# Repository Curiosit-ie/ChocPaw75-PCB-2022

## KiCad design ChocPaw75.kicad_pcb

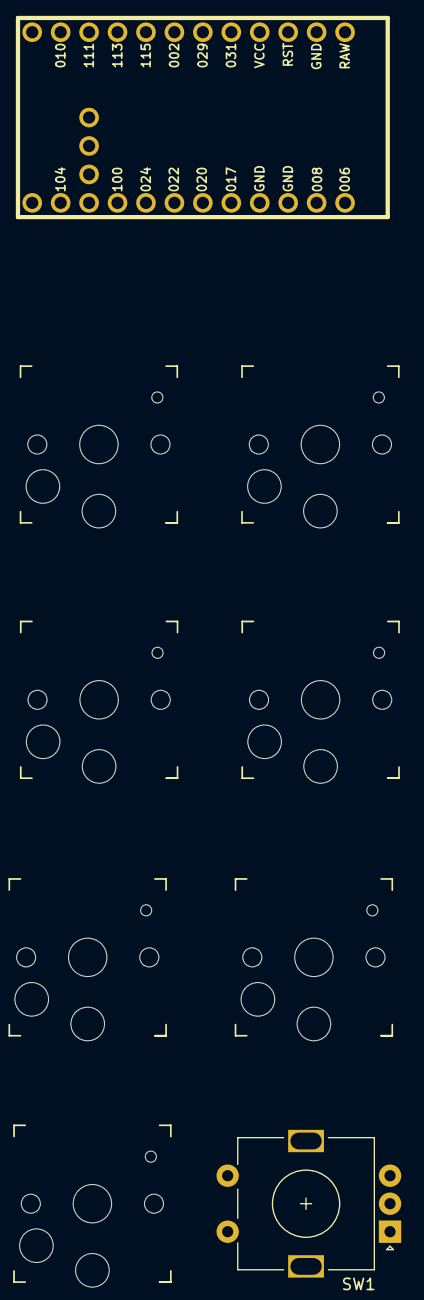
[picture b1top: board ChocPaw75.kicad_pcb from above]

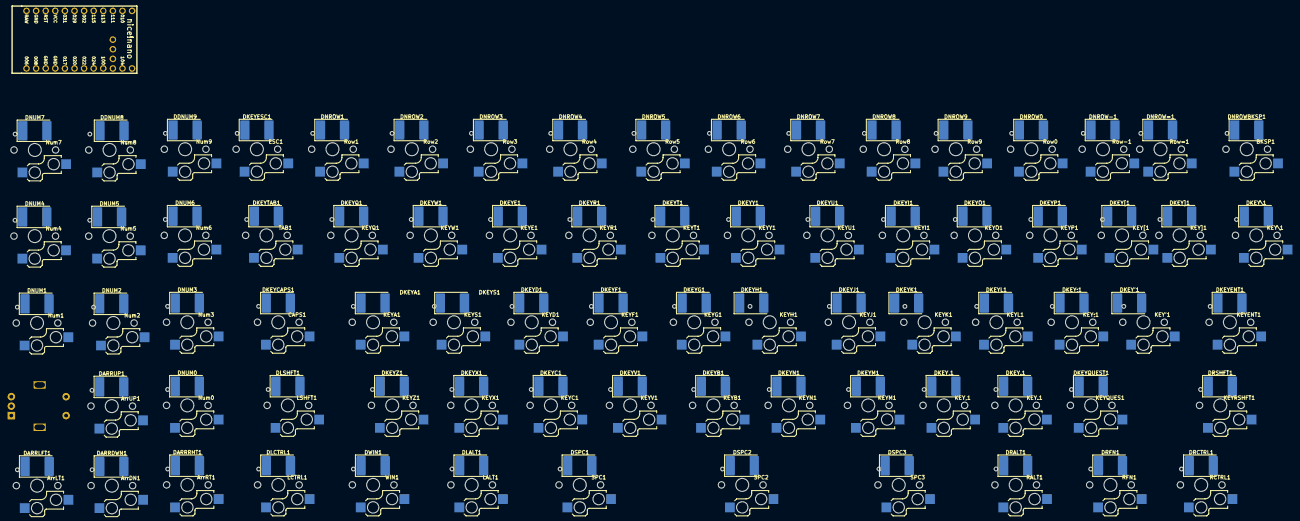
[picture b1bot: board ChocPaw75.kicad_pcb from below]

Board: 2 copper layers, 154 parts (77 on the bottom side), 98 nets, no tracks yet.

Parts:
ArrDN1: Arrow DOWN; Kailh_socket_PG1350
ArrLT1: Arrow LEFT; Kailh_socket_PG1350
ArrRT1: Arrow RIGHT; Kailh_socket_PG1350
ArrUP1: Arrow UP; Kailh_socket_PG1350
BKSP1: MX-LED; Kailh_socket_PG1350
CAPS1: MX-LED; Kailh_socket_PG1350
DARRDWN1: D_Small; D_3220_8050Metric
DARRLFT1: D_Small; D_3220_8050Metric
DARRRHT1: D_Small; D_3220_8050Metric
DARRUP1: D_Small; D_3220_8050Metric
DDNUM8, DDNUM9: D_Small; D_3220_8050Metric
DKEY'1: D_Small; D_3220_8050Metric
DKEY,1: D_Small; D_3220_8050Metric
DKEY.1: D_Small; D_3220_8050Metric
DKEY;1: D_Small; D_3220_8050Metric
DKEYA1: D_Small; D_3220_8050Metric
DKEYB1: D_Small; D_3220_8050Metric
DKEYC1: D_Small; D_3220_8050Metric
DKEYCAPS1: D_Small; D_3220_8050Metric
DKEYD1: D_Small; D_3220_8050Metric
DKEYE1: D_Small; D_3220_8050Metric
DKEYENT1: D_Small; D_3220_8050Metric
DKEYESC1: D_Small; D_3220_8050Metric
DKEYF1: D_Small; D_3220_8050Metric
DKEYG1: D_Small; D_3220_8050Metric
DKEYH1: D_Small; D_3220_8050Metric
DKEYI1: D_Small; D_3220_8050Metric
DKEYJ1: D_Small; D_3220_8050Metric
DKEYK1: D_Small; D_3220_8050Metric
DKEYL1: D_Small; D_3220_8050Metric
DKEYM1: D_Small; D_3220_8050Metric
DKEYN1: D_Small; D_3220_8050Metric
DKEYO1: D_Small; D_3220_8050Metric
DKEYP1: D_Small; D_3220_8050Metric
DKEYQ1: D_Small; D_3220_8050Metric
DKEYQUEST1: D_Small; D_3220_8050Metric
DKEYR1: D_Small; D_3220_8050Metric
DKEYS1: D_Small; D_3220_8050Metric
DKEYT1: D_Small; D_3220_8050Metric
DKEYTAB1: D_Small; D_3220_8050Metric
DKEYU1: D_Small; D_3220_8050Metric
DKEYV1: D_Small; D_3220_8050Metric
DKEYW1: D_Small; D_3220_8050Metric
DKEYX1: D_Small; D_3220_8050Metric
DKEYY1: D_Small; D_3220_8050Metric
DKEYZ1: D_Small; D_3220_8050Metric
DKEY[1: D_Small; D_3220_8050Metric
DKEY\1: D_Small; D_3220_8050Metric
DKEY]1: D_Small; D_3220_8050Metric
DLALT1: D_Small; D_3220_8050Metric
DLCTRL1: D_Small; D_3220_8050Metric
DLSHFT1: D_Small; D_3220_8050Metric
DNROW0, DNROW1, DNROW2, DNROW3, DNROW4, DNROW5, DNROW6, DNROW7, DNROW8, DNROW9: D_Small; D_3220_8050Metric
DNROW-1: D_Small; D_3220_8050Metric
DNROW=1: D_Small; D_3220_8050Metric
DNROWBKSP1: D_Small; D_3220_8050Metric
DNUM0, DNUM1, DNUM2, DNUM3, DNUM4, DNUM5, DNUM6, DNUM7: D_Small; D_3220_8050Metric
DRALT1: D_Small; D_3220_8050Metric
DRCTRL1: D_Small; D_3220_8050Metric
DRFN1: D_Small; D_3220_8050Metric
DRSHFT1: D_Small; D_3220_8050Metric
DSPC1, DSPC2, DSPC3: D_Small; D_3220_8050Metric
DWIN1: D_Small; D_3220_8050Metric
ESC1: MX-LED; Kailh_socket_PG1350
KEY'1: MX-LED; Kailh_socket_PG1350
KEY,1: MX-LED; Kailh_socket_PG1350
KEY.1: MX-LED; Kailh_socket_PG1350
KEY;1: MX-LED; Kailh_socket_PG1350
KEYA1: MX-LED; Kailh_socket_PG1350
KEYB1: MX-LED; Kailh_socket_PG1350
KEYC1: MX-LED; Kailh_socket_PG1350
KEYD1: MX-LED; Kailh_socket_PG1350
KEYE1: MX-LED; Kailh_socket_PG1350
KEYENT1: MX-LED; Kailh_socket_PG1350
KEYF1: MX-LED; Kailh_socket_PG1350
KEYG1: MX-LED; Kailh_socket_PG1350
KEYH1: MX-LED; Kailh_socket_PG1350
KEYI1: MX-LED; Kailh_socket_PG1350
KEYJ1: MX-LED; Kailh_socket_PG1350
KEYK1: MX-LED; Kailh_socket_PG1350
KEYL1: MX-LED; Kailh_socket_PG1350
KEYM1: MX-LED; Kailh_socket_PG1350
KEYN1: MX-LED; Kailh_socket_PG1350
KEYO1: MX-LED; Kailh_socket_PG1350
KEYP1: MX-LED; Kailh_socket_PG1350
KEYQ1: MX-LED; Kailh_socket_PG1350
KEYQUES1: MX-LED; Kailh_socket_PG1350
KEYR1: MX-LED; Kailh_socket_PG1350
KEYRSHFT1: MX-LED; Kailh_socket_PG1350
KEYS1: MX-LED; Kailh_socket_PG1350
KEYT1: MX-LED; Kailh_socket_PG1350
KEYU1: MX-LED; Kailh_socket_PG1350
KEYV1: MX-LED; Kailh_socket_PG1350
KEYW1: MX-LED; Kailh_socket_PG1350
KEYX1: MX-LED; Kailh_socket_PG1350
KEYY1: MX-LED; Kailh_socket_PG1350
KEYZ1: MX-LED; Kailh_socket_PG1350
KEY[1: MX-LED; Kailh_socket_PG1350
KEY\1: MX-LED; Kailh_socket_PG1350
KEY]1: MX-LED; Kailh_socket_PG1350
LALT1: MX-LED; Kailh_socket_PG1350
LCTRL1: MX-LED; Kailh_socket_PG1350
LSHFT1: MX-LED; Kailh_socket_PG1350
Num0: Num 0; Kailh_socket_PG1350
Num1: Num 1; Kailh_socket_PG1350
Num2: Num 2; Kailh_socket_PG1350
Num3: Num 3; Kailh_socket_PG1350
Num4: Num 4; Kailh_socket_PG1350
Num5: Num 5; Kailh_socket_PG1350
Num6: Num 6; Kailh_socket_PG1350
Num7: Num 7; Kailh_socket_PG1350
Num8: Num 8; Kailh_socket_PG1350
Num9: Num 9; Kailh_socket_PG1350
RALT1: MX-LED; Kailh_socket_PG1350
RCTRL1: MX-LED; Kailh_socket_PG1350
RFN1: MX-LED; Kailh_socket_PG1350
Row0, Row1, Row2, Row3, Row4, Row5, Row6, Row7, Row8, Row9: MX-LED; Kailh_socket_PG1350
Row-1: MX-LED; Kailh_socket_PG1350
Row=1: MX-LED; Kailh_socket_PG1350
SPC1, SPC2, SPC3: MX-LED; Kailh_socket_PG1350
SW1: RotaryEncoder; RotaryEncoder_Alps_EC11E-Switch_Vertical_H20mm
TAB1: MX-LED; Kailh_socket_PG1350
U1: nice_nano
WIN1: MX-LED; Kailh_socket_PG1350

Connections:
/Col 0: ArrLT1.1 (COL), Num1.1 (COL), Num4.1 (COL), Num7.1 (COL)
/Col 1: ArrDN1.1 (COL), ArrUP1.1 (COL), Num2.1 (COL), Num5.1 (COL), Num8.1 (COL)
/Col 2: ArrRT1.1 (COL), Num0.1 (COL), Num3.1 (COL), Num6.1 (COL), Num9.1 (COL)
/Col 4: KEYA1.1 (COL), KEYQ1.1 (COL), KEYZ1.1 (COL), Row1.1 (COL), WIN1.1 (COL)
/Col 5: KEYS1.1 (COL), KEYW1.1 (COL), KEYX1.1 (COL), LALT1.1 (COL), Row2.1 (COL)
/Col 6: KEYC1.1 (COL), KEYD1.1 (COL), KEYE1.1 (COL), Row3.1 (COL), SPC1.1 (COL)
/Col 7: KEYF1.1 (COL), KEYR1.1 (COL), KEYV1.1 (COL), Row4.1 (COL), SPC2.1 (COL)
/Col 8: KEYB1.1 (COL), KEYG1.1 (COL), KEYT1.1 (COL), Row5.1 (COL), SPC3.1 (COL)
/Col 9: KEYH1.1 (COL), KEYN1.1 (COL), KEYY1.1 (COL), RALT1.1 (COL), Row6.1 (COL)
/Col 10: KEYJ1.1 (COL), KEYM1.1 (COL), KEYU1.1 (COL), RFN1.1 (COL), Row7.1 (COL)
/Col 11: KEY,1.1 (COL), KEYI1.1 (COL), KEYK1.1 (COL), RCTRL1.1 (COL), Row8.1 (COL)
/Col 12: KEY.1.1 (COL), KEYL1.1 (COL), KEYO1.1 (COL), Row9.1 (COL)
/Col 13: KEY;1.1 (COL), KEYP1.1 (COL), KEYQUES1.1 (COL), Row0.1 (COL)
/Col 14: KEY'1.1 (COL), KEYRSHFT1.1 (COL), KEY[1.1 (COL), Row-1.1 (COL)
/Col 15: KEYENT1.1 (COL), KEY]1.1 (COL), Row=1.1 (COL)
/Col 16: BKSP1.1 (COL), KEY\1.1 (COL)
/Col 3: CAPS1.1 (COL), ESC1.1 (COL), LCTRL1.1 (COL), LSHFT1.1 (COL), TAB1.1 (COL)
/Row 0: DDNUM8.1 (K), DDNUM9.1 (K), DKEYESC1.1 (K), DNROW0.1 (K), DNROW1.1 (K), DNROW2.1 (K), DNROW3.1 (K), DNROW4.1 (K), DNROW5.1 (K), DNROW6.1 (K), DNROW7.1 (K), DNROW8.1 (K), DNROW9.1 (K), DNROW-1.1 (K), DNROW=1.1 (K), DNROWBKSP1.1 (K), DNUM7.1 (K)
/Row 1: DKEYE1.1 (K), DKEYI1.1 (K), DKEYO1.1 (K), DKEYP1.1 (K), DKEYQ1.2 (A), DKEYR1.1 (K), DKEYT1.1 (K), DKEYTAB1.1 (K), DKEYU1.1 (K), DKEYW1.1 (K), DKEYY1.1 (K), DKEY[1.1 (K), DKEY\1.1 (K), DKEY]1.1 (K), DNUM4.1 (K), DNUM5.1 (K), DNUM6.1 (K)
/Row 2: DKEY'1.1 (K), DKEY;1.1 (K), DKEYA1.1 (K), DKEYCAPS1.1 (K), DKEYD1.1 (K), DKEYENT1.1 (K), DKEYF1.1 (K), DKEYG1.1 (K), DKEYH1.1 (K), DKEYJ1.1 (K), DKEYK1.1 (K), DKEYL1.1 (K), DKEYS1.1 (K), DNUM1.1 (K), DNUM2.1 (K), DNUM3.1 (K)
/Row 3: DARRUP1.1 (K), DKEY,1.1 (K), DKEY.1.1 (K), DKEYB1.1 (K), DKEYC1.1 (K), DKEYM1.1 (K), DKEYN1.1 (K), DKEYQUEST1.1 (K), DKEYV1.1 (K), DKEYX1.1 (K), DKEYZ1.1 (K), DLSHFT1.1 (K), DNUM0.1 (K), DRSHFT1.1 (K)
/Row 4: DARRDWN1.1 (K), DARRLFT1.1 (K), DARRRHT1.1 (K), DLALT1.1 (K), DLCTRL1.1 (K), DRALT1.1 (K), DRCTRL1.1 (K), DRFN1.1 (K), DSPC1.1 (K), DSPC2.1 (K), DSPC3.1 (K), DWIN1.1 (K)
unnamed: ArrDN1.2 (ROW), DARRDWN1.2 (A)
unnamed: ArrLT1.2 (ROW), DARRLFT1.2 (A)
unnamed: ArrRT1.2 (ROW), DARRRHT1.2 (A)
unnamed: ArrUP1.2 (ROW), DARRUP1.2 (A)
unnamed: BKSP1.2 (ROW), DNROWBKSP1.2 (A)
unnamed: CAPS1.2 (ROW), DKEYCAPS1.2 (A)
unnamed: DDNUM8.2 (A), Num8.2 (ROW)
unnamed: DDNUM9.2 (A), Num9.2 (ROW)
unnamed: DKEY'1.2 (A), KEY'1.2 (ROW)
unnamed: DKEY,1.2 (A), KEY,1.2 (ROW)
unnamed: DKEY.1.2 (A), KEY.1.2 (ROW)
unnamed: DKEY;1.2 (A), KEY;1.2 (ROW)
unnamed: DKEYA1.2 (A), KEYA1.2 (ROW)
unnamed: DKEYB1.2 (A), KEYB1.2 (ROW)
unnamed: DKEYC1.2 (A), KEYC1.2 (ROW)
unnamed: DKEYD1.2 (A), KEYD1.2 (ROW)
unnamed: DKEYE1.2 (A), KEYE1.2 (ROW)
unnamed: DKEYENT1.2 (A), KEYENT1.2 (ROW)
unnamed: DKEYESC1.2 (A), ESC1.2 (ROW)
unnamed: DKEYF1.2 (A), KEYF1.2 (ROW)
unnamed: DKEYG1.2 (A), KEYG1.2 (ROW)
unnamed: DKEYH1.2 (A), KEYH1.2 (ROW)
unnamed: DKEYI1.2 (A), KEYI1.2 (ROW)
unnamed: DKEYJ1.2 (A), KEYJ1.2 (ROW)
unnamed: DKEYK1.2 (A), KEYK1.2 (ROW)
unnamed: DKEYL1.2 (A), KEYL1.2 (ROW)
unnamed: DKEYM1.2 (A), KEYM1.2 (ROW)
unnamed: DKEYN1.2 (A), KEYN1.2 (ROW)
unnamed: DKEYO1.2 (A), KEYO1.2 (ROW)
unnamed: DKEYP1.2 (A), KEYP1.2 (ROW)
unnamed: DKEYQ1.1 (K), KEYQ1.2 (ROW)
unnamed: DKEYQUEST1.2 (A), KEYQUES1.2 (ROW)
unnamed: DKEYR1.2 (A), KEYR1.2 (ROW)
unnamed: DKEYS1.2 (A), KEYS1.2 (ROW)
unnamed: DKEYT1.2 (A), KEYT1.2 (ROW)
unnamed: DKEYTAB1.2 (A), TAB1.2 (ROW)
unnamed: DKEYU1.2 (A), KEYU1.2 (ROW)
unnamed: DKEYV1.2 (A), KEYV1.2 (ROW)
unnamed: DKEYW1.2 (A), KEYW1.2 (ROW)
unnamed: DKEYX1.2 (A), KEYX1.2 (ROW)
unnamed: DKEYY1.2 (A), KEYY1.2 (ROW)
unnamed: DKEYZ1.2 (A), KEYZ1.2 (ROW)
unnamed: DKEY[1.2 (A), KEY[1.2 (ROW)
unnamed: DKEY\1.2 (A), KEY\1.2 (ROW)
unnamed: DKEY]1.2 (A), KEY]1.2 (ROW)
unnamed: DLALT1.2 (A), LALT1.2 (ROW)
unnamed: DLCTRL1.2 (A), LCTRL1.2 (ROW)
unnamed: DLSHFT1.2 (A), LSHFT1.2 (ROW)
unnamed: DNROW0.2 (A), Row0.2 (ROW)
unnamed: DNROW1.2 (A), Row1.2 (ROW)
unnamed: DNROW2.2 (A), Row2.2 (ROW)
unnamed: DNROW3.2 (A), Row3.2 (ROW)
unnamed: DNROW4.2 (A), Row4.2 (ROW)
unnamed: DNROW5.2 (A), Row5.2 (ROW)
unnamed: DNROW6.2 (A), Row6.2 (ROW)
unnamed: DNROW7.2 (A), Row7.2 (ROW)
unnamed: DNROW8.2 (A), Row8.2 (ROW)
unnamed: DNROW9.2 (A), Row9.2 (ROW)
unnamed: DNROW-1.2 (A), Row-1.2 (ROW)
unnamed: DNROW=1.2 (A), Row=1.2 (ROW)
unnamed: DNUM0.2 (A), Num0.2 (ROW)
unnamed: DNUM1.2 (A), Num1.2 (ROW)
unnamed: DNUM2.2 (A), Num2.2 (ROW)
unnamed: DNUM3.2 (A), Num3.2 (ROW)
unnamed: DNUM4.2 (A), Num4.2 (ROW)
unnamed: DNUM5.2 (A), Num5.2 (ROW)
unnamed: DNUM6.2 (A), Num6.2 (ROW)
unnamed: DNUM7.2 (A), Num7.2 (ROW)
unnamed: DRALT1.2 (A), RALT1.2 (ROW)
unnamed: DRCTRL1.2 (A), RCTRL1.2 (ROW)
unnamed: DRFN1.2 (A), RFN1.2 (ROW)
unnamed: DRSHFT1.2 (A), KEYRSHFT1.2 (ROW)
unnamed: DSPC1.2 (A), SPC1.2 (ROW)
unnamed: DSPC2.2 (A), SPC2.2 (ROW)
unnamed: DSPC3.2 (A), SPC3.2 (ROW)
unnamed: DWIN1.2 (A), WIN1.2 (ROW)

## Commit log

2022-10-13 20221013 pcb update
    pcb generally complete, needs refinement, borders, and mcu placement finalized
